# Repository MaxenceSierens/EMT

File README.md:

# EMT Dossier comportant des infos sur la partie code du projet joulemetre EMT 
Ce Readme donnera des infos sur comment utiliser le code...{
}

Utile Arduino : 
commande permettant de téléverser sur l'ide arduino avec linux(Attention à l'espace !!)
sudo chmod a+rw /dev/ttyACM0

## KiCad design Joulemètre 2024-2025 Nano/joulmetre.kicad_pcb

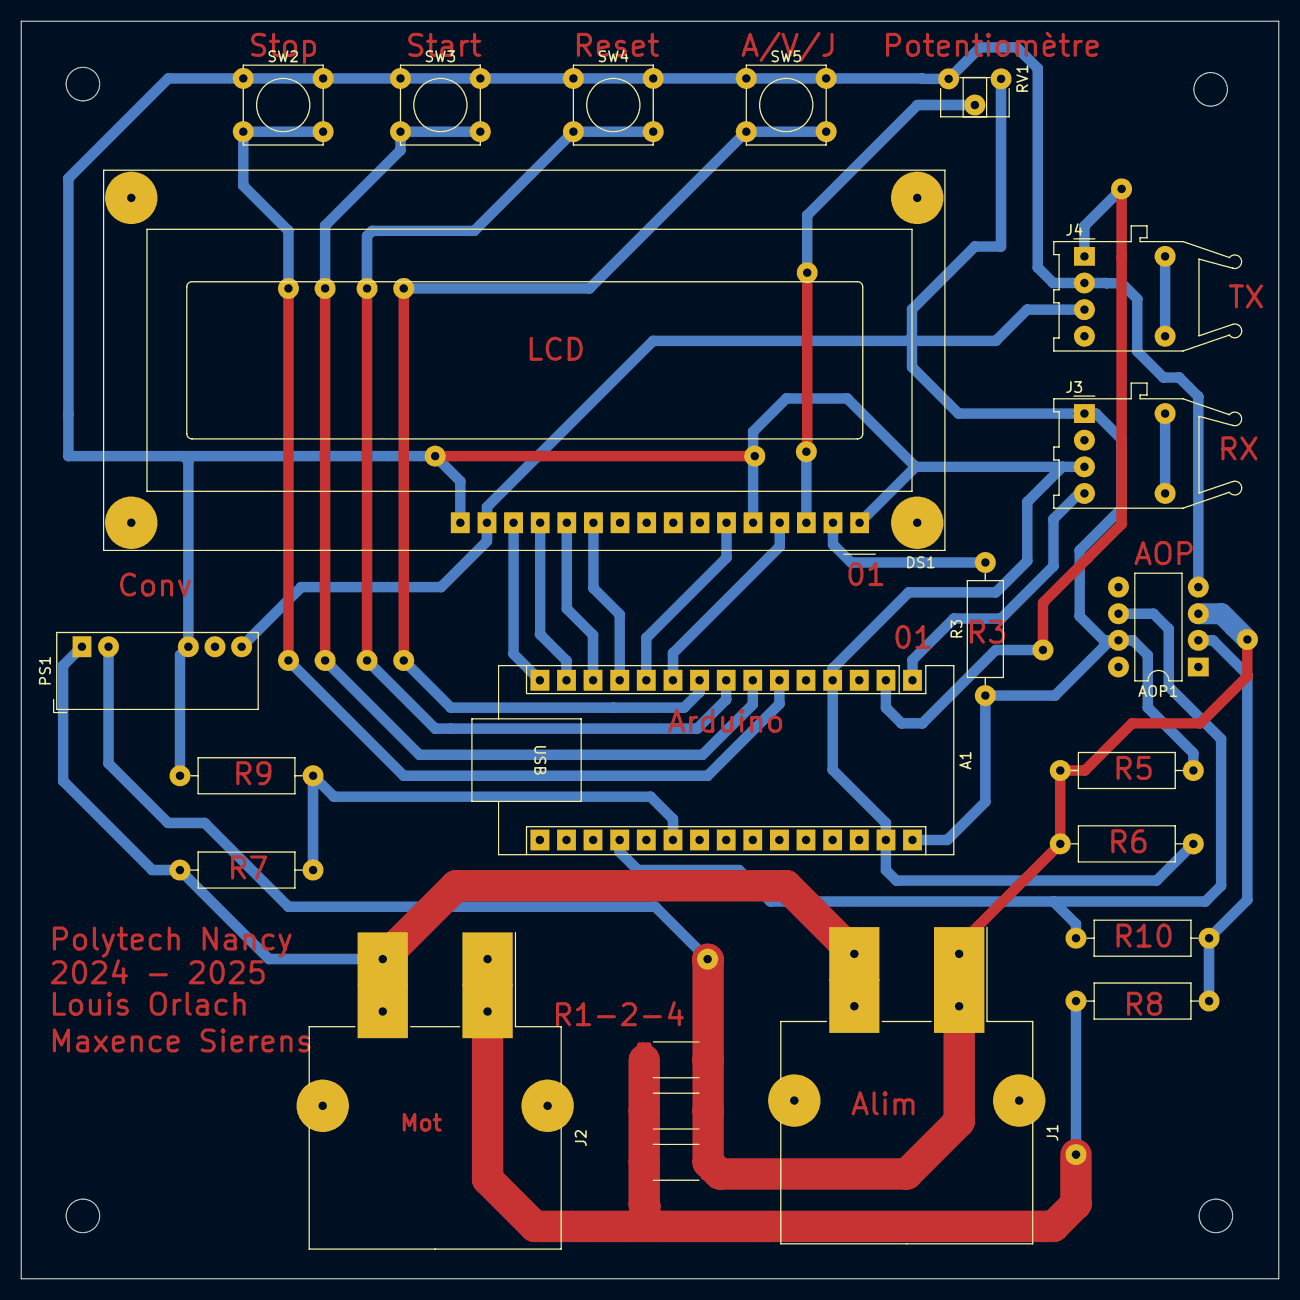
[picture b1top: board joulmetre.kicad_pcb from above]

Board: 2 copper layers, 120.0 x 120.0 mm, 23 parts (0 on the bottom side), 24 nets.

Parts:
A1: Arduino_Nano_ESP32; Arduino_Nano
AOP1: LTC1050; DIP-8_W7.62mm_LongPads
DS1: WC1602A
J1, J2: CONN_COUDE; Molex_Mini-Fit_Sr_42820-22XX_1x02_P10.00mm_Horizontal
J3: AFBR-1624Z; Broadcom_AFBR-16xxZ_Horizontal
J4: AFBR-2624Z; Broadcom_AFBR-16xxZ_Horizontal
PS1: IH4803SH; Converter_DCDC_XP_POWER-IHxxxxSH_THT
R1, R2, R4: 20m; R_2512_6332Metric_Pad1.40x3.35mm_HandSolder
R3: 220; R_Axial_DIN0309_L9.0mm_D3.2mm_P12.70mm_Horizontal
R5: 2,2K; R_Axial_DIN0309_L9.0mm_D3.2mm_P12.70mm_Horizontal
R6: 270R; R_Axial_DIN0309_L9.0mm_D3.2mm_P12.70mm_Horizontal
R7: 100K; R_Axial_DIN0309_L9.0mm_D3.2mm_P12.70mm_Horizontal
R8: 1K; R_Axial_DIN0309_L9.0mm_D3.2mm_P12.70mm_Horizontal
R9: 10k; R_Axial_DIN0309_L9.0mm_D3.2mm_P12.70mm_Horizontal
R10: 10K; R_Axial_DIN0309_L9.0mm_D3.2mm_P12.70mm_Horizontal
RV1: R_Pot; Potentiometer_ACP_CA6-H2,5_Horizontal
SW2: Stop; SW_Tactile_Straight_KSA0Axx1LFTR
SW3: Start; SW_Tactile_Straight_KSA0Axx1LFTR
SW4: reset; SW_Tactile_Straight_KSA0Axx1LFTR
SW5: A/V/J; SW_Tactile_Straight_KSA0Axx1LFTR

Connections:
+5V: A1.30 (VIN), AOP1.7 (V+), DS1.15 (LED(+)), J3.1 (VCCT), J4.3 (VCCR), PS1.7 (+Vout), R3.1, R5.2, RV1.1
GND: A1.4 (GND), A1.29 (GND), AOP1.4 (V-), DS1.1 (VSS), DS1.5 (R/W), DS1.16 (LED(-)), J3.3 (VEET), J4.2 (VEER), PS1.5 (-Vout), R6.1, R9.2, RV1.3, SW2.1, SW3.1, SW4.1, SW5.1
MOT-: J2.1 (VCC1), R1.2, R2.2, R4.2, R8.2
unnamed: A1.19 (A0), AOP1.6, R10.1
unnamed: A1.21 (A2), R7.1, R9.1
unnamed: A1.2 (D0/RX), J4.1 (Data_Out)
unnamed: A1.1 (D1/TX), J3.4 (Data_in)
unnamed: A1.6 (D3), SW2.2
unnamed: A1.7 (D4), SW3.2
unnamed: A1.8 (D5), SW4.2
unnamed: A1.9 (D6), SW5.2
unnamed: A1.10 (D7), DS1.4 (RS)
unnamed: A1.11 (D8), DS1.6 (E)
unnamed: A1.12 (D9), DS1.11 (D4)
unnamed: A1.13 (D10/CS), DS1.12 (D5)
unnamed: A1.14 (D11/COPI), DS1.13 (D6)
unnamed: A1.15 (D12/CIPO), DS1.14 (D7)
unnamed: AOP1.2 (-), R8.1, R10.2
unnamed: DS1.2 (VDD), R3.2
unnamed: DS1.3 (VO), RV1.2
unnamed: J3.5 (HP), J3.8 (HP)
unnamed: J4.5 (HP), J4.8 (HP)
VBAT+: J1.2 (VCC2), J2.2 (VCC2), PS1.1 (+Vin), R7.2
VBAT-: AOP1.3 (+), J1.1 (VCC1), PS1.2 (-Vin), R1.1, R2.1, R4.1, R5.1, R6.2

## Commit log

2024-10-22 Dadacsheet arduino
2024-11-12 code complet
2024-11-12 code d'affichage sur lcd (slide)
2024-11-12 vieux code complet
2024-11-19 Create Questions
2024-11-19 Update Questions
2024-11-19 2023 code final
2024-11-26 Données de la clée USB
2025-01-28 Code_Final_2025
2025-02-04 Code_final_04/02
2025-03-04 Code _utilisé
2025-03-19 Update sketch_nov19c.ino 19/03/2025
